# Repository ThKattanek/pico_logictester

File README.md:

# 🔌 Pico Logic Tester

> **Ein portabler 16-Kanal Logic Tester basierend auf dem Raspberry Pi Pico**

Der Pico Logic Tester ist ein handliches Debugging-Tool für Hardware-Entwickler. Er ersetzt die klassischen Test-LEDs und zeigt bis zu 16 digitale Signale gleichzeitig in Echtzeit auf einem farbigen TFT-Display an.

<div style="text-align: left; margin-left: 0; padding-left: 0;">

</div>

*Der Pico Logic Tester in Aktion*

---

## Key Features

| Feature | Beschreibung |
|---------|-------------|
| **16 Logic Inputs** | GPIO 6-17, 20-22, 26-27 |
| **1,77" TFT Display** | 128x160 Pixel, 16-bit Farbe |
| **Akku-betrieben** | Li-Ion mit USB-C Laden |
| **3.3V & 5V tolerant** | Sichere Eingangsstufe |
| **Echtzeit-Anzeige** | <10ms Reaktionszeit |
| **Open Source** | Hardware & Software frei verfügbar |

---

## 🛠️ Technische Daten

### Hardware Specs
| Komponente | Spezifikation |
|------------|---------------|
| **MCU** | Raspberry Pi Pico (RP2040/RP2350) |
| **Display** | ST7735S, 128×160, SPI |
| **Eingänge** | 16× Digital, 0-5V |
| **Stromversorgung** | 3.7V Li-Ion Akku |
| **Gehäuse** | 120×80×25mm (3D-druckbar) |
| **Gewicht** | ~150g |

### Performance
- **Scan-Rate:** 200Hz (5ms pro Zyklus)
- **Logic Levels:** LOW <0.8V, HIGH >2.5V 
- **Akkulaufzeit:** ~8-12 Stunden aktiv
- **Display-Update:** Nur bei Änderungen (optimiert)

---

## 🚀 Quick Start

### 1. Hardware Setup
```
1. Akku über USB-C laden (grüne LED = voll)
2. Logic Tester einschalten (kurzer Power-Button Druck)
3. GND-Referenz mit Testobjekt verbinden
4. Testleitungen an Eingänge 0-15 anschließen
```

### 2. Display Interpretation

| Anzeige | Bedeutung |
|---------|-----------|
| **Grüne Box** | Logic HIGH (>2.5V) |
| **Schwarze Box** | Logic LOW (<0.8V) |
| **Grün/Gelb/Rot** | Batteriestatus |

### 3. Ein/Ausschalten
- **EIN:** Kurzer Tastendruck (<1s)
- **AUS:** Langer Tastendruck (>2s)
- **Auto-OFF:** Bei kritischem Batteriestand

---

## 📁 Repository Struktur

```
pico_logictester/
├── README.md                    # Diese Datei
├── LICENSE                      # GPL v2 Lizenz
├── firmware/                    # Pico C++ Firmware
│   ├── src/main.cpp               # Hauptprogramm
│   ├── CMakeLists.txt             # Build Config
│   └── include/displaylib_16/     # Display Treiber
├── hardware/                    # KiCad PCB Design
│   ├── pico_logictester.kicad_*   # Schaltplan & Layout
│   ├── gerber/                    # Produktionsdaten
│   └── bom/                       # Interaktive Stückliste
└── doc/                         # Dokumentation
    ├── pico_logictester_dokumentation.md  # Vollständige Doku
    ├── pico_logictester_dokumentation.pdf # PDF Version
    └── images/                     # Bilder & Diagramme
```

---

## 🔨 Build & Flash

### Voraussetzungen
- **Pico SDK** (v2.2.0+)
- **CMake** (v3.13+) 
- **ARM GCC Toolchain**

### Kompilierung
```bash
cd firmware
mkdir build && cd build
cmake ..
make -j4
```

### Programmierung
```bash
# UF2 auf Pico kopieren (BOOTSEL Mode)
cp pico_logictester.uf2 /media/<user>/RPI-RP2/

# Oder mit picotool
picotool load pico_logictester.uf2
```

---

## 📸 Screenshots

<table>
<tr>
<td align="center">
<br>
<b>Logic HIGH Signale</b>
</td>
<td align="center">
<br>
<b>PCB Design</b>
</td>
</tr>
</table>

---

## 📚 Dokumentation

| Dokument | Beschreibung | Format |
|----------|--------------|--------|
| 📋 **[Vollständige Dokumentation](doc/pico_logictester_dokumentation.md)** | Detaillierte Hardware/Software Beschreibung | Markdown |
| 📄 **[PDF Version](doc/pico_logictester_dokumentation.pdf)** | Druckbare Dokumentation | PDF |
| 🔧 **[Hardware BOM](hardware/bom/pico_logictester_pcb_1.0_ibom.html)** | Interaktive Stückliste | HTML |

### Was Sie in der Dokumentation finden:
- **Hardware-Design:** Schaltplan, PCB-Layout, Stückliste
- **Software-Architektur:** C++ Code-Struktur, Performance-Optimierungen  
- **Benutzerhandbuch:** Bedienung, Fehlerbehebung, Kalibrierung
- **Fertigung:** PCB-Produktion, 3D-Druck Gehäuse
- **Entwicklung:** Build-System, Debugging, Erweiterungen

---

## Beitragen

Contributions sind willkommen!

### Wie Sie helfen können:
- **Bug Reports:** Issues über GitHub melden
- **Feature Requests:** Neue Ideen vorschlagen  
- **Code:** Pull Requests für Verbesserungen
- **Dokumentation:** Rechtschreibfehler, Übersetzungen
- **Testing:** Hardware-Tests, Kompatibilitätsprüfung

### Development Workflow:
```bash
1. Fork das Repository
2. Feature Branch erstellen (`git checkout -b feature/amazing-feature`)
3. Änderungen committen (`git commit -m 'Add amazing feature'`)
4. Branch pushen (`git push origin feature/amazing-feature`)
5. Pull Request öffnen
```

---

## 📜 Lizenz

Dieses Projekt steht unter der **GNU General Public License v2.0**.

- ✅ **Kommerzieller Einsatz erlaubt**
- ✅ **Modifikation erlaubt** 
- ✅ **Distribution erlaubt**
- ❗ **Quellcode muss verfügbar sein**
- ❗ **Gleiche Lizenz für Ableitungen**

Siehe [LICENSE](LICENSE) für Details.

---

## Show your Support

Wenn Ihnen dieses Projekt gefällt:
- **Star** das Repository
- **Fork** für eigene Experimente  
- **Teilen** mit anderen Hardware-Hackern
- **Feedback** über Issues

---

## 📞 Kontakt & Support

| Kanal | Link | Beschreibung |
|-------|------|--------------|
| 👤 **Autor** | Thorsten Kattanek | Hardware & Software Development |
| 📧 **E-Mail** | thorsten@kattanek.de | Direkte Fragen & Support |
| 🐙 **GitHub** | [ThKattanek/pico_logictester](https://github.com/ThKattanek/pico_logictester) | Source Code & Issues |
| 🐛 **Bug Reports** | [GitHub Issues](https://github.com/ThKattanek/pico_logictester/issues) | Bugs & Feature Requests |

---

<div align="center">

**Made with ❤️ for Hardware Debugging**

*Happy Coding!*

</div>

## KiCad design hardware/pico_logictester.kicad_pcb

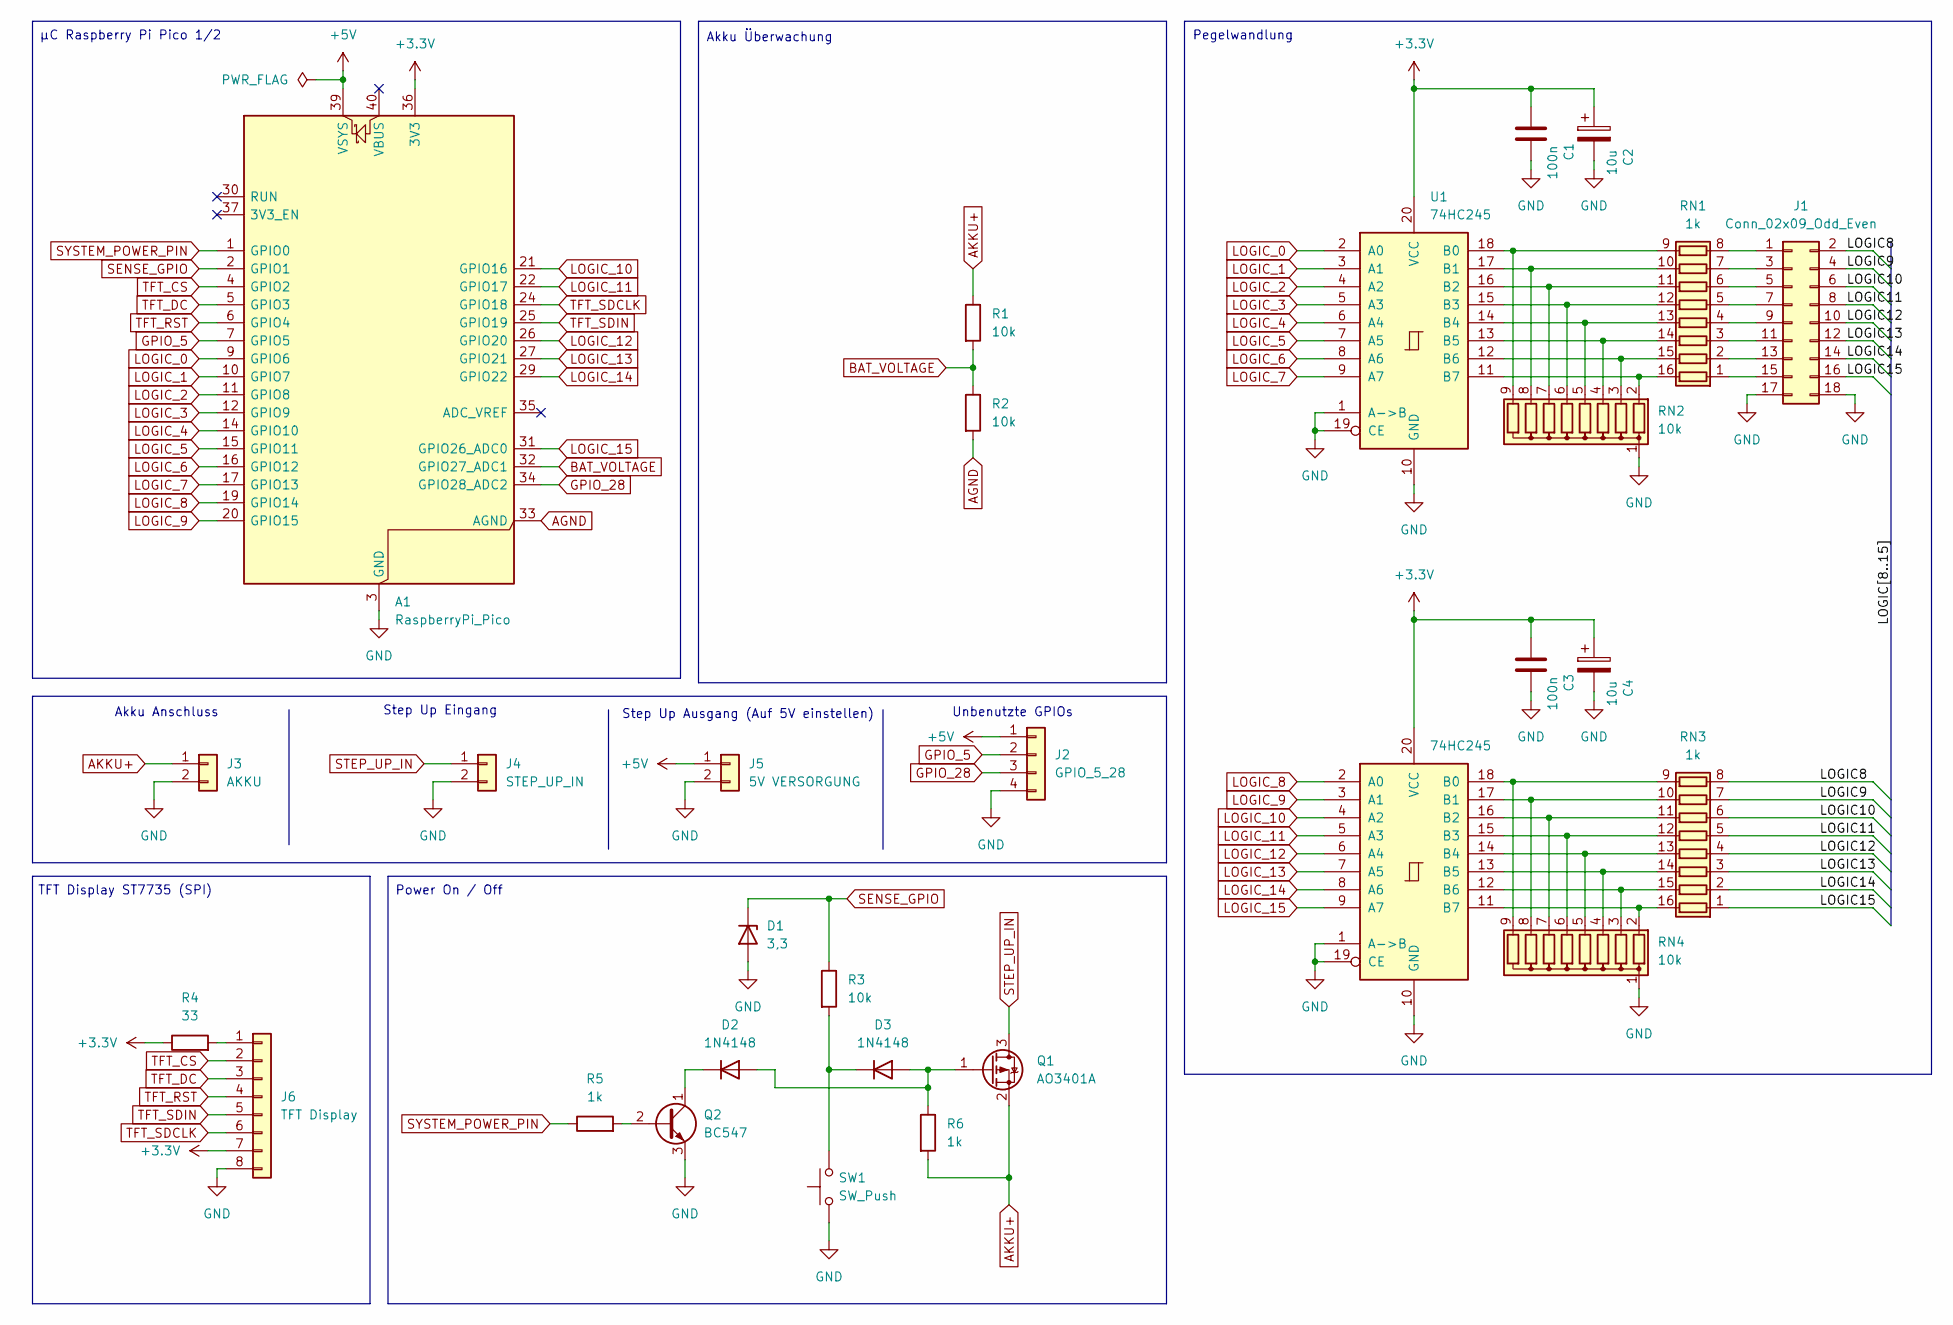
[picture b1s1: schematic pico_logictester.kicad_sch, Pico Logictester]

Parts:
A1: RaspberryPi_Pico; RaspberryPi_Pico_Common_Unspecified
C1, C3: 100n; C_0805_2012Metric_Pad1.18x1.45mm_HandSolder
C2, C4: 10u; CP_Elec_4x5.4
D1: 3,3; D_DO-35_SOD27_P7.62mm_Horizontal
D2, D3: 1N4148; D_DO-35_SOD27_P7.62mm_Horizontal
J1: Conn_02x09_Odd_Even; IDC-Header_2x09_P2.54mm_Horizontal
J2: GPIO_5_28; PinHeader_1x04_P2.54mm_Vertical
J3: AKKU; PinHeader_1x02_P2.54mm_Vertical
J4: STEP_UP_IN; PinHeader_1x02_P2.54mm_Vertical
J5: 5V VERSORGUNG; PinHeader_1x02_P2.54mm_Vertical
J6: TFT Display; PinSocket_1x08_P2.54mm_Vertical
Q1: AO3401A; SOT-23
Q2: BC547; TO-92_Inline
R1, R2, R3: 10k; R_0805_2012Metric_Pad1.20x1.40mm_HandSolder
R4: 33; R_0805_2012Metric_Pad1.20x1.40mm_HandSolder
R5, R6: 1k; R_0805_2012Metric_Pad1.20x1.40mm_HandSolder
RN1, RN3: 1k; R_Array_Convex_8x0602
RN2, RN4: 10k; R_Array_SIP9
SW1: SW_Push; SW_PUSH_6mm_H9.5mm
U1, U2: 74HC245; TSSOP-20_4.4x6.5mm_P0.65mm

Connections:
+3.3V: A1.36 (3V3), C1.1, C2.1, C3.1, C4.1, J6.7, R4.1, U1.20 (VCC), U2.20 (VCC)
+5V: A1.39 (VSYS), J2.1, J5.1
/LOGIC8: J1.2, RN3.8 (R8.1)
/LOGIC9: J1.4, RN3.7 (R7.1)
/LOGIC10: J1.6, RN3.6 (R6.1)
/LOGIC11: J1.8, RN3.5 (R5.1)
/LOGIC12: J1.10, RN3.4 (R4.1)
/LOGIC13: J1.12, RN3.3 (R3.1)
/LOGIC14: J1.14, RN3.2 (R2.1)
/LOGIC15: J1.16, RN3.1 (R1.1)
AGND: A1.33 (AGND), R2.2
AKKU+: J3.1, Q1.2 (S), R1.1, R6.2
BAT_VOLTAGE: A1.32 (GPIO27_ADC1), R1.2, R2.1
GND: A1.3 (GND), A1.8 (GND), A1.13 (GND), A1.18 (GND), A1.23 (GND), A1.28 (GND), A1.38 (GND), C1.2, C2.2, C3.2, C4.2, D1.2 (A), J1.17, J1.18, J2.4, J3.2, J4.2, J5.2, J6.8, Q2.3 (E), RN2.1 (common), RN4.1 (common), SW1.1, U1.1 (A->B), U1.10 (GND), U1.19 (CE), U2.1 (A->B), U2.10 (GND), U2.19 (CE)
GPIO_5: A1.7 (GPIO5), J2.2
GPIO_28: A1.34 (GPIO28_ADC2), J2.3
LOGIC_0: A1.9 (GPIO6), U1.2 (A0)
LOGIC_1: A1.10 (GPIO7), U1.3 (A1)
LOGIC_2: A1.11 (GPIO8), U1.4 (A2)
LOGIC_3: A1.12 (GPIO9), U1.5 (A3)
LOGIC_4: A1.14 (GPIO10), U1.6 (A4)
LOGIC_5: A1.15 (GPIO11), U1.7 (A5)
LOGIC_6: A1.16 (GPIO12), U1.8 (A6)
LOGIC_7: A1.17 (GPIO13), U1.9 (A7)
LOGIC_8: A1.19 (GPIO14), U2.2 (A0)
LOGIC_9: A1.20 (GPIO15), U2.3 (A1)
LOGIC_10: A1.21 (GPIO16), U2.4 (A2)
LOGIC_11: A1.22 (GPIO17), U2.5 (A3)
LOGIC_12: A1.26 (GPIO20), U2.6 (A4)
LOGIC_13: A1.27 (GPIO21), U2.7 (A5)
LOGIC_14: A1.29 (GPIO22), U2.8 (A6)
LOGIC_15: A1.31 (GPIO26_ADC0), U2.9 (A7)
unnamed: D2.2 (A), D3.2 (A), Q1.1 (G), R6.1
unnamed: D2.1 (K), Q2.1 (C)
unnamed: D3.1 (K), R3.2, SW1.2
unnamed: J1.1, RN1.8 (R8.1)
unnamed: J1.3, RN1.7 (R7.1)
unnamed: J1.5, RN1.6 (R6.1)
unnamed: J1.7, RN1.5 (R5.1)
unnamed: J1.9, RN1.4 (R4.1)
unnamed: J1.11, RN1.3 (R3.1)
unnamed: J1.13, RN1.2 (R2.1)
unnamed: J1.15, RN1.1 (R1.1)
unnamed: J6.1, R4.2
unnamed: Q2.2 (B), R5.2
unnamed: RN1.16 (R1.2), RN2.2 (R1), U1.11 (B7)
unnamed: RN1.15 (R2.2), RN2.3 (R2), U1.12 (B6)
unnamed: RN1.14 (R3.2), RN2.4 (R3), U1.13 (B5)
unnamed: RN1.13 (R4.2), RN2.5 (R4), U1.14 (B4)
unnamed: RN1.12 (R5.2), RN2.6 (R5), U1.15 (B3)
unnamed: RN1.11 (R6.2), RN2.7 (R6), U1.16 (B2)
unnamed: RN1.10 (R7.2), RN2.8 (R7), U1.17 (B1)
unnamed: RN1.9 (R8.2), RN2.9 (R8), U1.18 (B0)
unnamed: RN3.16 (R1.2), RN4.2 (R1), U2.11 (B7)
unnamed: RN3.15 (R2.2), RN4.3 (R2), U2.12 (B6)
unnamed: RN3.14 (R3.2), RN4.4 (R3), U2.13 (B5)
unnamed: RN3.13 (R4.2), RN4.5 (R4), U2.14 (B4)
unnamed: RN3.12 (R5.2), RN4.6 (R5), U2.15 (B3)
unnamed: RN3.11 (R6.2), RN4.7 (R6), U2.16 (B2)
unnamed: RN3.10 (R7.2), RN4.8 (R7), U2.17 (B1)
unnamed: RN3.9 (R8.2), RN4.9 (R8), U2.18 (B0)
SENSE_GPIO: A1.2 (GPIO1), D1.1 (K), R3.1
STEP_UP_IN: J4.1, Q1.3 (D)
SYSTEM_POWER_PIN: A1.1 (GPIO0), R5.1
TFT_CS: A1.4 (GPIO2), J6.2
TFT_DC: A1.5 (GPIO3), J6.3
TFT_RST: A1.6 (GPIO4), J6.4
TFT_SDCLK: A1.24 (GPIO18), J6.6
TFT_SDIN: A1.25 (GPIO19), J6.5

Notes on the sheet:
Pegelwandlung
Unbenutzte GPIOs
µC Raspberry Pi Pico 1/2
Step Up Ausgang (Auf 5V einstellen)
Step Up Eingang
TFT Display ST7735 (SPI)
Akku Anschluss
Akku Überwachung
Power On / Off

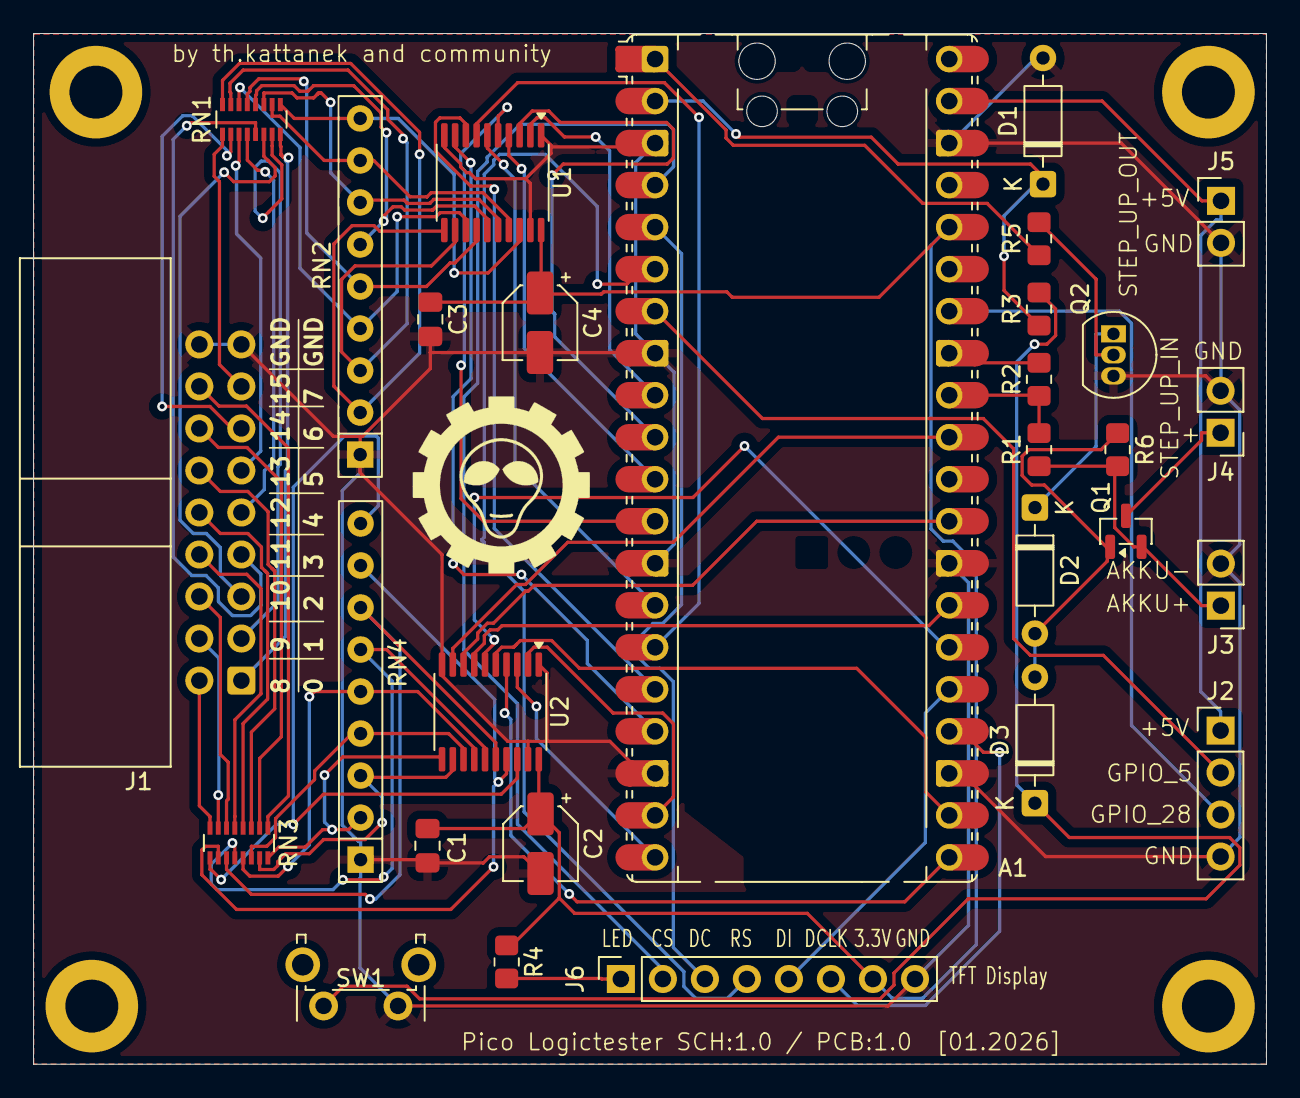
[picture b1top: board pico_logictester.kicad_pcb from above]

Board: 2 copper layers, 74.5 x 62.3 mm, 33 parts (0 on the bottom side), 69 nets.

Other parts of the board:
REF1, REF2, REF3, REF4: MountingHole_3.2mm_M3_DIN965_Pad

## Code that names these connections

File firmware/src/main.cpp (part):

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
// Display GPIO and SPI configuration
// SPI0 
#define TFT_CS_PIN    2     // Chip Select pin
#define TFT_DC_PIN    3     // Data/Command pin
#define TFT_RST_PIN   4     // Reset pin
#define TFT_SDIN_PIN  19    // Master Out Slave In pin
#define TFT_SCLK_PIN   18   // Serial Clock pin   

#define TFT_WIDTH     128   // Display width in pixels
#define TFT_HEIGHT    160   // Display height in pixels

// Power management pins
#define SYSTEM_POWER_PIN 0    // Controls PNP transistor to keep system powered ()
#define POWER_BUTTON_PIN 1    // Power button input

// Battery monitoring
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void InitPowerManagement()
{
    // Initialize power control pin - keep power on (HIGH for PNP transistor)
    gpio_init(SYSTEM_POWER_PIN);
    gpio_set_dir(SYSTEM_POWER_PIN, GPIO_OUT);
    gpio_put(SYSTEM_POWER_PIN, 1); // HIGH = PNP conducts = MOSFET conducts = power on
    
    // Initialize power button pin with pull-up
    gpio_init(POWER_BUTTON_PIN);
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    sleep_ms(1000);
    
    // Turn off power control pin (LOW = PNP blocks = MOSFET blocks = power off)
    gpio_put(SYSTEM_POWER_PIN, 0);
    
    // If we get here, hardware shutdown failed - go to infinite loop
    while(true) {
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    
    // Initialize display with faster SPI speed
    tft_display.TFTInitSPIType(16000, spi0); // Increased from 8000 to 16MHz for faster display updates
    tft_display.setupGPIO(TFT_RST_PIN, TFT_DC_PIN, TFT_CS_PIN, TFT_SCLK_PIN, TFT_SDIN_PIN);
    tft_display.TFTInitPCBType(ST7735_TFT::TFT_ST7735S_Black); // Initialize for BLACK Tab PCB
    tft_display.TFTInitScreenSize(0, 0, TFT_WIDTH, TFT_HEIGHT);
    tft_display.setRotation(displaylib_16_graphics::Degrees_90);
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
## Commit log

2026-01-14 start repo
2026-01-15 hardware: start
2026-01-15 hardware: Eingänge beschaltet, und tft angeschlossen
2026-01-17 hardware: Alle baugruppen im schaltplan hinzugefügt.
2026-01-17 firmware: spannungswerte für battery überwachung auf 3.7 für Low und 3.5 zum Abschalten gesetzt.
2026-01-20 hardware: Schaltplan fertig gestellt und Footprints zugeordnet
2026-01-22 Autorouting im Livestream. noch 6 offene Verbindungen!
2026-01-24 hardware: ERC Error behoben
2026-01-24 hardware: new pcb layout
2026-01-24 remove files
2026-01-24 hardware: bauckup
2026-01-24 hardware: pcb_1.0 fertig gestellt und Gerberfiles erstellt.
2026-01-25 hardware: Interaktive BOM hinzugefügt (mit PlugIn: Interactive Html Bom)
2026-01-25 doc: Schaltplan v1.0 als PDF hinzugefügt
2026-02-21 On Board LED wird beim Start des Pico eingeschaltet. Als Indikator das der Pico und die Firmware läuft.
2026-02-21 Dokumentation erweitert.
2026-02-21 Squashed commit of the following:
    commit bb0bbc1d573e0b7ef0f2029c41a12eb1b7a3b53d
    Author: Thorsten Kattanek <thorsten.kattanek@gmx.de>
    Date: Sat Feb 21 18:10:56 2026 +0100
    Update README.md
    commit 1b0319603f573a80e1201760700dad0fea377821
    Author: Thorsten Kattanek <thorsten.kattanek@gmx.de>
2026-02-21 Neues FreeCad Projekt für das Case
2026-02-21 Angefangen die obere Hälfte des Gehäuses zu erstellen.
2026-02-28 Angefangen die unterer Gehäusehälfte zu erstellen.
2026-03-03 Hinweis im Schaltplan hinzugefügt. D2 kann entfallen, und wird nicht benötigt.
2026-03-07 Gehäuse endlich fertig! Hoffentlich :)
2026-03-12 4x Fase noch dran gemacht
2026-03-12 Case: 4x Durchmesser 2,5 auf 2,0 geändert. Halterung für TFT Display
2026-03-21 Gehäuse nochmal ein wenig angepasst. Verschiedene Durchmesser geändert + Abstandshalter seitlich mit Gehäuse Verbunden, da sie sonst leicht abbrechen können.
2026-03-21 Bilder vom fertigen Produkt hinzugefügt.
